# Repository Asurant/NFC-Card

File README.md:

# NFC-Card
An NFC card that links back to my github <br/>

With this NFC card I can more freely share my contacts with others and it also acts as a cool way to show my github.<br/>
<br/>
Future Change Plans:<br/>
&emsp;Adding a personal website onto the card (I don't have one yet)<br/>
&emsp;Adding my irl name, number, and email (If done I don't be adding this onto the github for privacy reasons)<br/>
<br/>
Front: <br/>
 <br/> <br/>
Back:<br/>
<br/>
<br/>
Disclaimer:<br/>
This was made with the support of the NFC card tutorial at https://jams.hackclub.com/jam/hacker-card<br/>
This is a submission for an event known as Blueprint. Check it out here https://blueprint.hackclub.com/r/56?ref=r <br/>
<br/><br/>
BTW<br/>
Bottom Left Symbol on card is the Justiciar symbol from Lord Of The Mysteries / Lord Of Mysteries / Guǐ Mì Zhī Zhǔ <br/>
The Symbol on the right side is the Sun symbol from the same series.

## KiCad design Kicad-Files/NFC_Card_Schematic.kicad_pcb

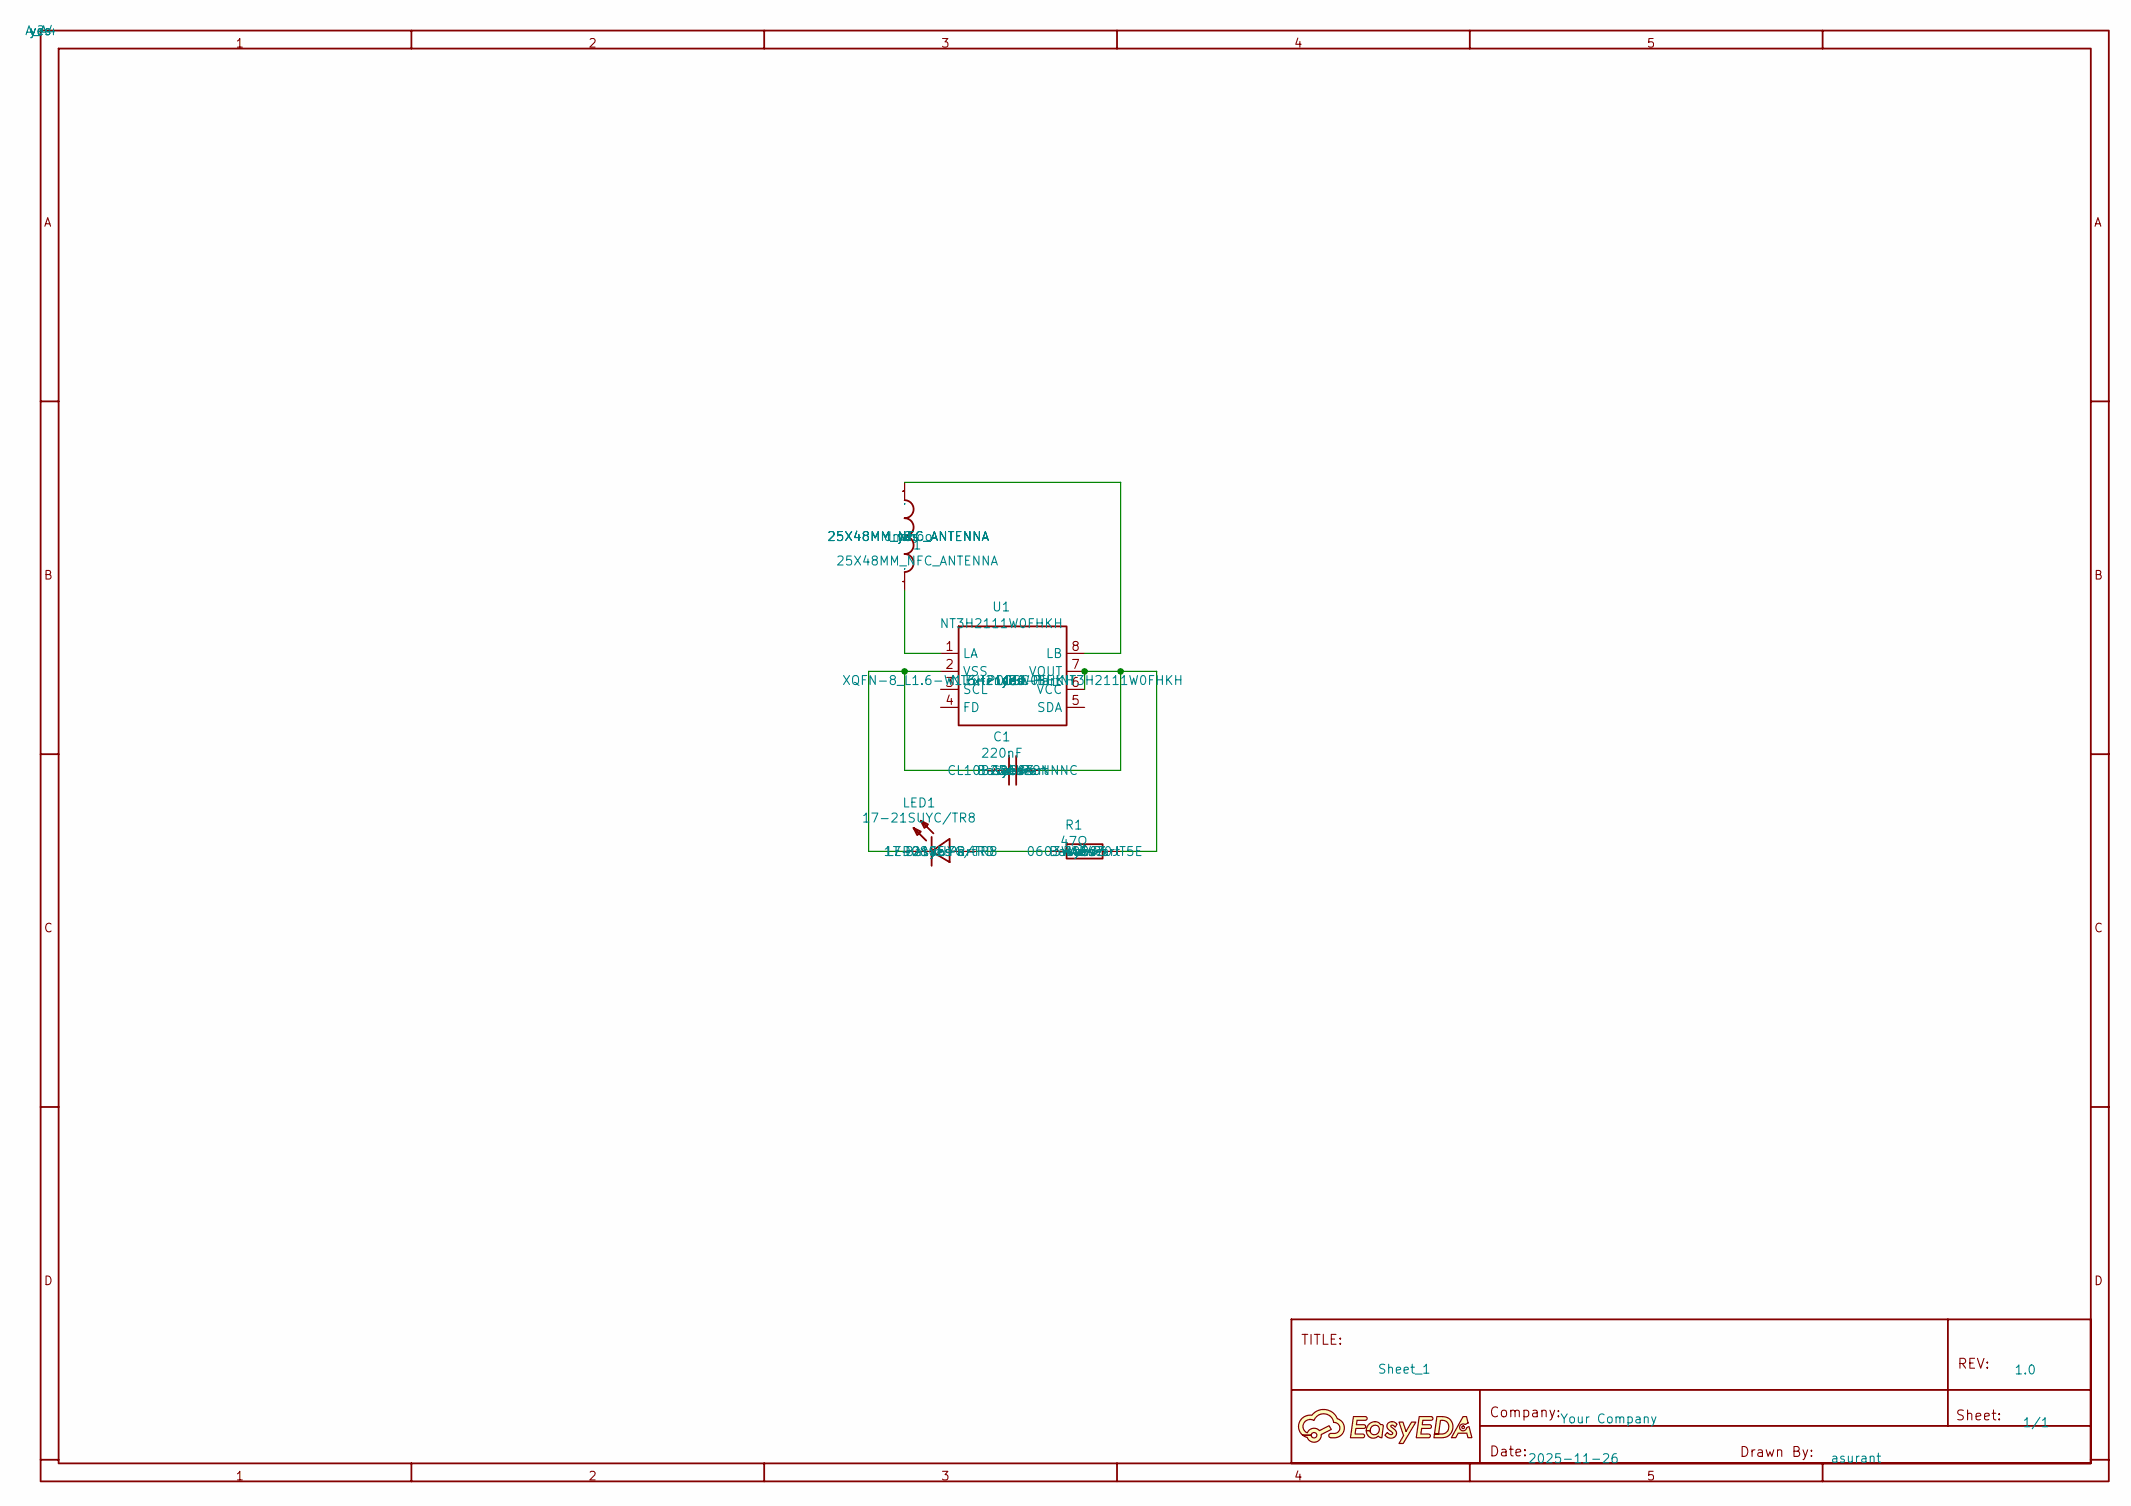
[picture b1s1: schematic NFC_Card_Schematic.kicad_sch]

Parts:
1: 25X48MM_NFC_ANTENNA
C1: 220nF; C0603; Manufacturer Part CL10B224KA8NNNC; JLCPCB Part Class Basic Part
LED1: 17-21SUYC/TR8; LED0805-R-RD; Manufacturer Part KT-0805黄灯; JLCPCB Part Class Basic Part
R1: 47Ω; R0603; Manufacturer Part 0603WAF470JT5E; JLCPCB Part Class Basic Part
U1: NT3H2111W0FHKH; XQFN-8_L1.6-W1.6-P0.50-BL_NT3H2111W0FHKH; Manufacturer Part NT3H2111W0FHKH; JLCPCB Part Class Extended Part

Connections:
LED1_1: LED1.1 (+), R1.1
U1_1: 1.P$2, U1.1 (LA)
U1_2: C1.1, LED1.2 (-), U1.2 (VSS)
U1_3: U1.3 (SCL)
U1_4: U1.4 (FD)
U1_5: U1.5 (SDA)
U1_7: C1.2, R1.2, U1.6 (VCC), U1.7 (VOUT)
U1_8: 1.P$1, U1.8 (LB)

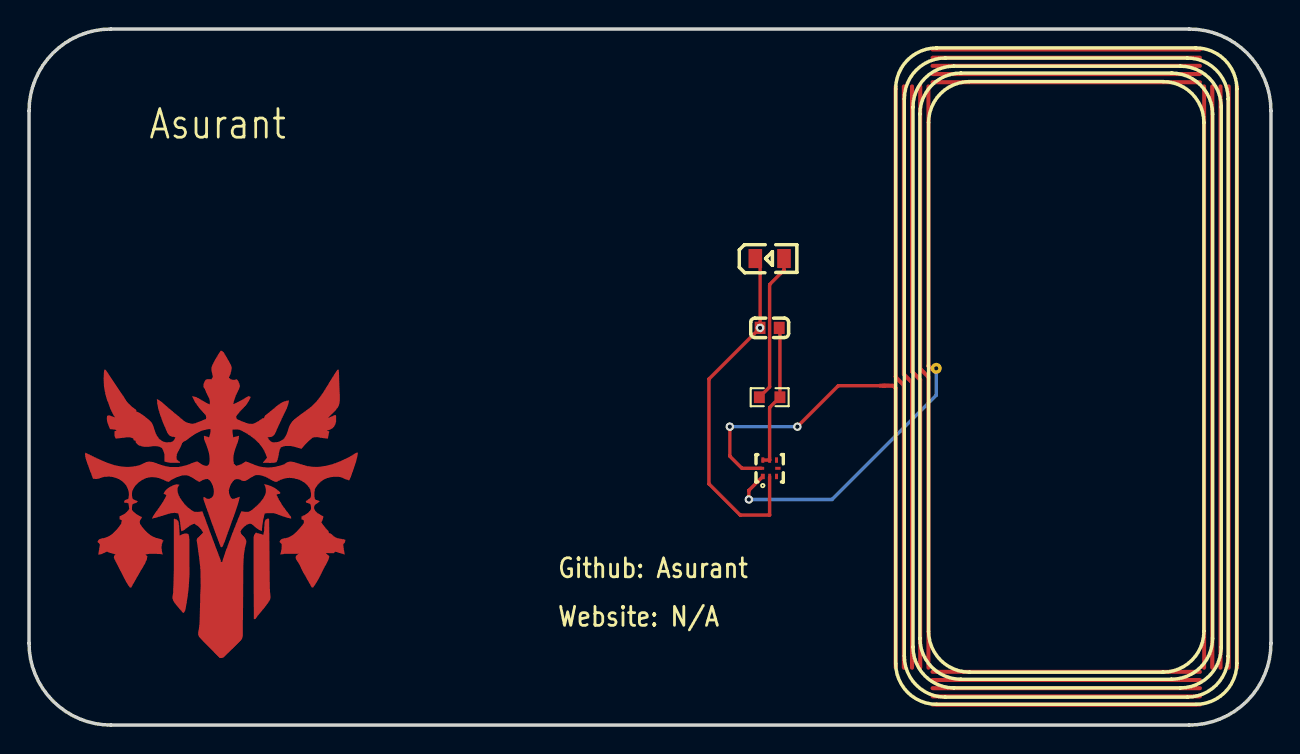
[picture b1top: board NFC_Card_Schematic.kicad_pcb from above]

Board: 2 copper layers, 91.0 x 51.0 mm, 5 parts (0 on the bottom side), 5 nets.

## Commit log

2025-12-01 Create temp
